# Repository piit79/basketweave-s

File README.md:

# Basketweave-S

Through-hole Alice-style keyboard with arrow keys, symmetric 3-key macro clusters, and a rotary encoder

Based on the [Basketweave](https://github.com/null-l/basketweave) by [null-l](https://github.com/null-l)

### Default Layout

> View on [Keyboard Layout Editor](http://www.keyboard-layout-editor.com/#/gists/975ace00974ba7fb16d758d6a68e5321)

### BOM and Build Guide
[Build Guide](doc/build.md)

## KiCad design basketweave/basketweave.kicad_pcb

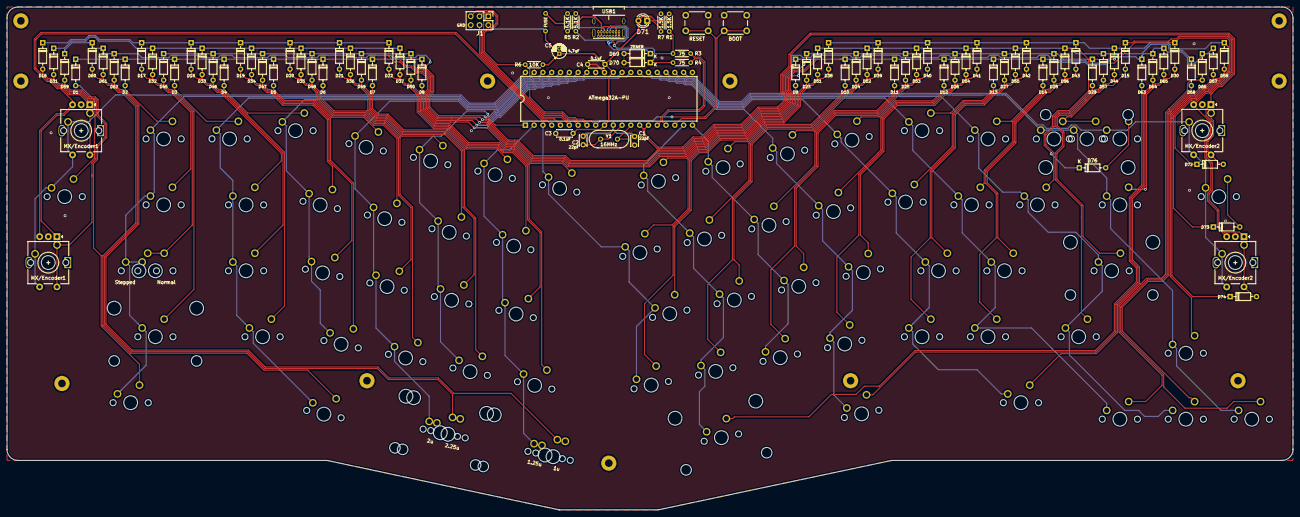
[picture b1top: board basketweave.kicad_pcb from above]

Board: 2 copper layers, 371.5 x 145.3 mm, 187 parts (0 on the bottom side), 114 nets.

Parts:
C1, C2: 22pF; C_Disc_D3.0mm_W2.0mm_P2.50mm
C3, C4: 0.1uF; C_Disc_D4.3mm_W1.9mm_P5.00mm
C5: 4.7uF; CP_Radial_D4.0mm_P1.50mm
D1, D2, D3, D4, D5, D6, D7, D8, D9, D10, D11, D12, D13, D14, D15, D16, D17, D18, D19, D20, D21, D22, D23, D24, D25, D26, D27, D28, D29, D30, D31, D32, D33, D34, D35, D36, D37, D38, D39, D40, D41, D42, D43, D44, D45, D46, D47, D48, D49, D50, D51, D52, D53, D54, D55, D56, D57, D58, D59, D60, D61, D62, D63, D64, D65, D66, D67, D68, D72, D73, D74, D76: D_Small; D_DO-35_SOD27_P7.62mm_Horizontal
D69, D70: 3.6V; D_DO-35_SOD27_P7.62mm_Horizontal
D71: LED; LED_D3.0mm_Clear
F1: 500mA; polyfuse_5.1mm
H1, H2, H3, H4, H5, H6, H7, H8, H9, H11, H13: MountingHole; MountingHole_2.2mm_M2_Pad
J1: AVR-ISP-6; PinHeader_2x03_P2.54mm_Vertical
MX1, MX2, MX3, MX4, MX5, MX6, MX7, MX8, MX9, MX10, MX11, MX12, MX13, MX14, MX16, MX18, MX19, MX20, MX21, MX22, MX23, MX24, MX25, MX26, MX27, MX28, MX29, MX31, MX34, MX35, MX36, MX37, MX38, MX39, MX40, MX41, MX42, MX43, MX44, MX47, MX48, MX49, MX50, MX51, MX52, MX53, MX54, MX55, MX56, MX57, MX59, MX67, MX68, MX69, MX71, MX72, MX73, MX74, MX75, MX76: MX-NoLED; MXOnly-1U-NoLED
MX15: MX-NoLED; MXOnly-2U-NoLED
MX17, MX30, MX60, MX61, MX65, MX66: MX-NoLED; MXOnly-1.5U-NoLED
MX32, MX63: MX-NoLED; MXOnly-1.25U-NoLED
MX33, MX58: MX-NoLED; MXOnly-1.75U-NoLED
MX45, MX46, MX70: MX-NoLED; MXOnly-2.25U-ReversedStabilizers-NoLED
MX62: MX-NoLED; MXOnly-2U-ReversedStabilizers-NoLED
MX64: MX-NoLED; MXOnly-2.75U-ReversedStabilizers-NoLED
PATTERN1: Pattern_Left; pattern_left
PATTERN2: Pattern_Right; pattern_right
R1, R7: 1.5K; R_Axial_DIN0204_L3.6mm_D1.6mm_P5.08mm_Horizontal
R2, R5: 5.1K; R_Axial_DIN0204_L3.6mm_D1.6mm_P5.08mm_Horizontal
R3, R4: 75; R_Axial_DIN0204_L3.6mm_D1.6mm_P5.08mm_Horizontal
R6: 10K; R_Axial_DIN0204_L3.6mm_D1.6mm_P5.08mm_Horizontal
SW1: BOOT; SW_PUSH_6mm
SW2: RESET; SW_PUSH_6mm
SW3, SW4, SW5, SW6: Rotary_Encoder_Switch; RotaryEncoder_Alps_EC11E-Switch_Vertical_H20mm-for-MX
U1: ATmega32A-PU; DIP-40_W15.24mm
USB1: GCT-USB-4085-GF-A; USB_C_GCT_USB4085
Y1: 16Mhz; Crystal_HC49-4H_Vertical

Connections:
+5V: C3.1, C4.1, C5.1, D71.2, F1.1, J1.2, R1.1, R6.1, U1.10, U1.30
COL0: MX1.1, MX16.1, MX75.1, SW3.S1, SW5.S1, U1.40
COL1: MX2.1, MX17.1, MX32.1, MX33.1, MX46.1, MX60.1, U1.39
COL2: MX3.1, MX18.1, MX34.1, MX47.1, MX61.1, U1.38
COL3: MX4.1, MX19.1, MX35.1, MX48.1, U1.37
COL4: MX5.1, MX20.1, MX36.1, MX49.1, MX62.1, MX70.1, U1.36
COL5: MX6.1, MX21.1, MX37.1, MX50.1, U1.1
COL6: MX7.1, MX22.1, MX38.1, MX51.1, MX63.1, MX71.1, U1.2
COL7: MX8.1, MX23.1, MX39.1, MX52.1, U1.3
COL8: MX9.1, MX24.1, MX40.1, MX53.1, MX64.1, U1.19
COL9: MX10.1, MX25.1, MX41.1, MX54.1, U1.20
COL10: MX11.1, MX26.1, MX42.1, MX55.1, MX65.1, U1.27
COL11: MX12.1, MX27.1, MX43.1, MX56.1, MX66.1, U1.26
COL12: MX13.1, MX28.1, MX44.1, MX57.1, MX67.1, U1.25
COL13: MX14.1, MX29.1, MX45.1, MX58.1, MX68.1, U1.24
COL14: MX15.1, MX30.1, MX31.1, MX59.1, MX69.1, U1.23
COL15: MX72.1, MX73.1, MX74.1, MX76.1, SW4.S1, SW6.S1, U1.22
D+: R4.1, U1.16
D-: R3.1, U1.17
EN_A1: SW3.A, SW5.A, U1.4
EN_A2: SW3.B, SW5.B, U1.5
EN_B1: SW4.A, SW6.A, U1.15
EN_B2: SW4.B, SW6.B, U1.14
GND: C1.1, C2.1, C3.2, C4.2, C5.2, D69.2, D70.2, J1.6, R2.1, R5.1, R7.2, SW1.1, SW2.1, SW3.C, SW4.C, SW5.C, SW6.C, U1.11, U1.31, USB1.A1, USB1.A12, USB1.B1, USB1.B12, USB1.S1
MISO: J1.1, U1.7
MOSI: J1.4, U1.6
unnamed: C1.2, U1.13, Y1.1
unnamed: C2.2, U1.12, Y1.2
unnamed: D1.2, MX1.2, SW5.S2
unnamed: D2.2, MX2.2
unnamed: D3.2, MX3.2
unnamed: D4.2, MX4.2
unnamed: D5.2, MX5.2
unnamed: D6.2, MX6.2
unnamed: D7.2, MX7.2
unnamed: D8.2, MX8.2
unnamed: D9.2, MX9.2
unnamed: D10.2, MX10.2
unnamed: D11.2, MX11.2
unnamed: D12.2, MX12.2
unnamed: D13.2, MX13.2
unnamed: D14.2, MX14.2
unnamed: D15.2, MX15.2, MX31.2
unnamed: D16.2, MX16.2
unnamed: D17.2, MX17.2
unnamed: D18.2, MX18.2
unnamed: D19.2, MX19.2
unnamed: D20.2, MX20.2
unnamed: D21.2, MX21.2
unnamed: D22.2, MX22.2
unnamed: D23.2, MX23.2
unnamed: D24.2, MX24.2
unnamed: D25.2, MX25.2
unnamed: D26.2, MX26.2
unnamed: D27.2, MX27.2
unnamed: D28.2, MX28.2
unnamed: D29.2, MX29.2
unnamed: D30.2, MX30.2
unnamed: D31.2, MX75.2, SW3.S2
unnamed: D32.2, MX32.2, MX33.2
unnamed: D33.2, MX34.2
unnamed: D34.2, MX35.2
unnamed: D35.2, MX36.2
unnamed: D36.2, MX37.2
unnamed: D37.2, MX38.2
unnamed: D38.2, MX39.2
unnamed: D39.2, MX40.2
unnamed: D40.2, MX41.2
unnamed: D41.2, MX42.2
unnamed: D42.2, MX43.2
unnamed: D43.2, MX44.2
unnamed: D44.2, MX45.2
unnamed: D45.2, MX46.2
unnamed: D46.2, MX47.2
unnamed: D47.2, MX48.2
unnamed: D48.2, MX49.2
unnamed: D49.2, MX50.2
unnamed: D50.2, MX51.2
unnamed: D51.2, MX52.2
unnamed: D52.2, MX53.2
unnamed: D53.2, MX54.2
unnamed: D54.2, MX55.2
unnamed: D55.2, MX56.2
unnamed: D56.2, MX57.2
unnamed: D57.2, MX58.2
unnamed: D58.2, MX59.2
unnamed: D59.2, MX60.2
unnamed: D60.2, MX61.2
unnamed: D61.2, MX62.2, MX70.2
unnamed: D62.2, MX63.2, MX71.2
unnamed: D63.2, MX64.2
unnamed: D64.2, MX65.2
unnamed: D65.2, MX66.2
unnamed: D66.2, MX67.2
unnamed: D67.2, MX68.2
unnamed: D68.2, MX69.2
unnamed: D69.1, R1.2, R3.2, USB1.A7, USB1.B7
unnamed: D70.1, R4.2, USB1.A6, USB1.B6
unnamed: D71.1, R7.1
unnamed: D72.2, MX72.2, SW6.S2
unnamed: D73.2, MX73.2
unnamed: D74.2, MX74.2, SW4.S2
unnamed: D76.2, MX76.2
unnamed: R2.2, USB1.A5
unnamed: R5.2, USB1.B5
ROW0: D1.1, D2.1, D3.1, D4.1, D5.1, D6.1, D7.1, D8.1, D9.1, D10.1, D11.1, D12.1, D13.1, D14.1, D15.1, D72.1, U1.34
ROW1: D16.1, D17.1, D18.1, D19.1, D20.1, D21.1, D22.1, D23.1, D24.1, D25.1, D26.1, D27.1, D28.1, D29.1, D30.1, D73.1, U1.28
ROW2: D31.1, D32.1, D33.1, D34.1, D35.1, D36.1, D37.1, D38.1, D39.1, D40.1, D41.1, D42.1, D43.1, D44.1, D58.1, D74.1, U1.29
ROW3: D45.1, D46.1, D47.1, D48.1, D49.1, D50.1, D51.1, D52.1, D53.1, D54.1, D55.1, D56.1, D57.1, D68.1, D76.1, U1.33
ROW4: D59.1, D60.1, D61.1, D62.1, D63.1, D64.1, D65.1, D66.1, D67.1, U1.35
SCK: J1.3, U1.8
VCC: F1.2, USB1.A4, USB1.A9, USB1.B4, USB1.B9
boot: SW1.2, U1.18
reset: J1.5, R6.2, SW2.2, U1.9

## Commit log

2021-01-29 Remove and ignore sch/pcb backup files
2021-01-29 Move macro keys to the right and encoder to the left
2021-02-22 Make macro keys symmetric on both sides; move encoder to the left
2021-02-22 Replace gerbers with JLCPCB-friendly ones; add gerber zips
2021-07-10 Update build guide
2021-07-10 Replace the acrylic cover file
2021-07-10 Add back PCB patterns above diodes
2021-07-10 Add second rotary encoder on the right
2021-07-10 Change encoder plate cutout to standard MX one
2021-07-10 Add footprint library for the bottom plate
2021-07-10 Update gerbers
2021-09-17 Add support for encoders in the top macro positions
2021-09-17 Modify plate logo for Basketweave-S and move it into PCB footprint library
2021-09-17 Modify bottom plate logo for Basketweave-S and move it into PCB footprint library
2021-09-18 Add support for split backspace
2021-12-08 Update build.md
    Guide updated for Basketweave-S 1.8 with new pictures and added/removed/modified a few steps. It still needs a few pictures I forgot to take for the end.
2022-03-16 Enlarge right space cutout; fix position according to PCB
2022-03-30 Add via definition
